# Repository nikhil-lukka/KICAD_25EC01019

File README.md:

[Exercise 0: Pre-KiCad SPICE Verification (LTspice)]

* Circuit Modeling (L1): Simulated a discrete CMOS inverter utilizing Q1

  (2N7000 NMOS) and Q2 (BS250 PMOS) driving an output LED and current-limiting

  resistor (R1) at VDD = 5 V.

* DC Transfer Analysis (L2): Swept VIN from 0 V to 5 V (0.01 V steps) to

  extract the switching threshold Vm (VOUT = VDD/2) and evaluated dead-zone

  behavior at VDD = 5 V vs. VDD = 9 V.

* Transient & Load Metrics (L3): Measured static LED current (I_LED) at

  VIN = 0 V against theoretical (VDD - V_F)/R1, and extracted 10-90% rise (t_r)

  and fall (t_f) times using a 1 kHz pulse input.

* Python Post-Processing & Scaling Comparison (L4-L5): Reproduced the Voltage

  Transfer Characteristic (VTC) at 300 DPI via pandas and compared normalized

  VTC curves (VOUT/VDD vs. VIN/VDD) against a 65 nm integrated CMOS inverter.

[Exercise 1: Schematic Capture & ERC (KiCad Schematic Editor)]

* Constructed the full circuit schematic (<roll>_INV.kicad_sch) with Q2 oriented

  so its source connects to the +5V rail.

* Configured power distribution nets (+5V, GND) with PWR_FLAG symbols and

  routed wiper (POT_W) and input (VIN) nets to header J2.

* Verified schematic integrity with 0 ERC errors and 0 warnings.

[Exercise 2: Footprint Assignment & Pinout Verification]

* Cross-referenced physical package pinouts (Source, Gate, Drain) from the

  manufacturer datasheets for the 2N7000 and BS250 against KiCad symbol pin

  numbering.

* Assigned all eight component footprints and synchronized schematic changes

  to the PCB editor (F8) with 0 errors and 0 warnings.

[Exercise 3: PCB Layout, Routing & DRC (KiCad PCB Editor)]

* Board Geometry: Defined a 50 x 40 mm board outline on Edge.Cuts with four M3

  mounting holes inset 4 mm from the corners.

* Routing & Copper Pour: Assigned +5V and GND to a dedicated Power net class,

  routed all signal/power tracks, and poured a bottom-layer (B.Cu) ground

  plane with thermal reliefs.

* Silkscreen & Verification: Added board identification (CMOS INVERTER and

  roll number) on F.Silkscreen (>= 1 mm clearance from board edges) and achieved

  0 DRC violations, 0 unconnected items, and 0 schematic parity errors.

[Exercise 4: Manufacturing Outputs (GerbView & BOM)]

* Generated Gerber plot files and drill files into gerbers/.

* Visually inspected alignment, drill hits, and silkscreen layers in GerbView.

* Exported the Bill of Materials (CSV) and packaged the fabrication archive

  (<roll>_INV_gerbers.zip).

[Exercise 5: Design Explorations (Optional)]

* Explored single-variable hardware modifications through simulation, layout,

  and Gerber generation:

  1. Cascading a second inverter stage to form a non-inverting buffer.

  2. Reconfiguring the LED load to active-low operation.

  3. Increasing minimum trace/copper clearance to 0.4 mm for low-cost

     fabrication rules.

  4. Replacing the onboard trimpot with a 2-pin external input header and

     minimizing board area.

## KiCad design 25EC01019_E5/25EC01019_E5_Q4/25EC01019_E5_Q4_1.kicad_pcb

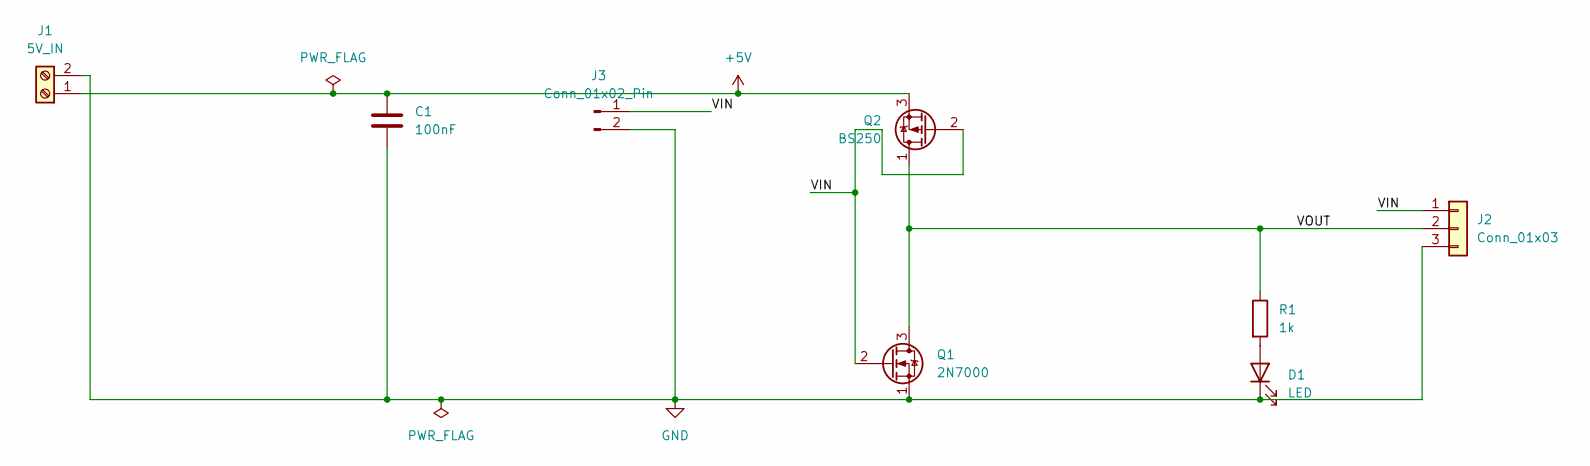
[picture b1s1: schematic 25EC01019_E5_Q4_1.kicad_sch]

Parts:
C1: 100nF; C_Disc_D5.0mm_W2.5mm_P5.00mm
D1: LED; LED_D3.0mm
J1: 5V_IN; TerminalBlock_Phoenix_MKDS-1,5-2-5.08_1x02_P5.08mm_Horizont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
J2: Conn_01x03; PinHeader_1x03_P2.54mm_Vertical
J3: Conn_01x02_Pin; PinHeader_1x02_P2.54mm_Vertical
Q1: 2N7000; TO-92_Inline
Q2: BS250; TO-92_Inline
R1: 1k; R_Axial_DIN0207_L6.3mm_D2.5mm_P10.16mm_Horizontal

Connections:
+5V: C1.1, J1.1, Q2.3 (S)
/VIN: J2.1, J3.1, Q1.2 (G), Q2.2 (G)
/VOUT: J2.2, Q1.3 (D), Q2.1 (D), R1.1
GND: C1.2, D1.1 (K), J1.2, J2.3, J3.2, Q1.1 (S)
unnamed: D1.2 (A), R1.2

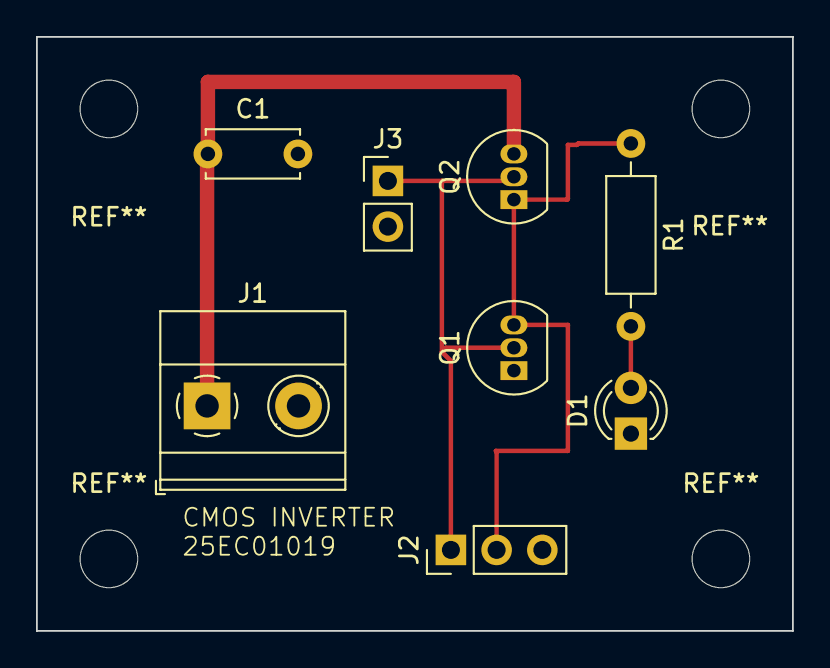
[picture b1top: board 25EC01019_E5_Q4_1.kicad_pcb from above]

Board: 2 copper layers, 42.0 x 33.0 mm, 8 parts (0 on the bottom side), 5 nets.

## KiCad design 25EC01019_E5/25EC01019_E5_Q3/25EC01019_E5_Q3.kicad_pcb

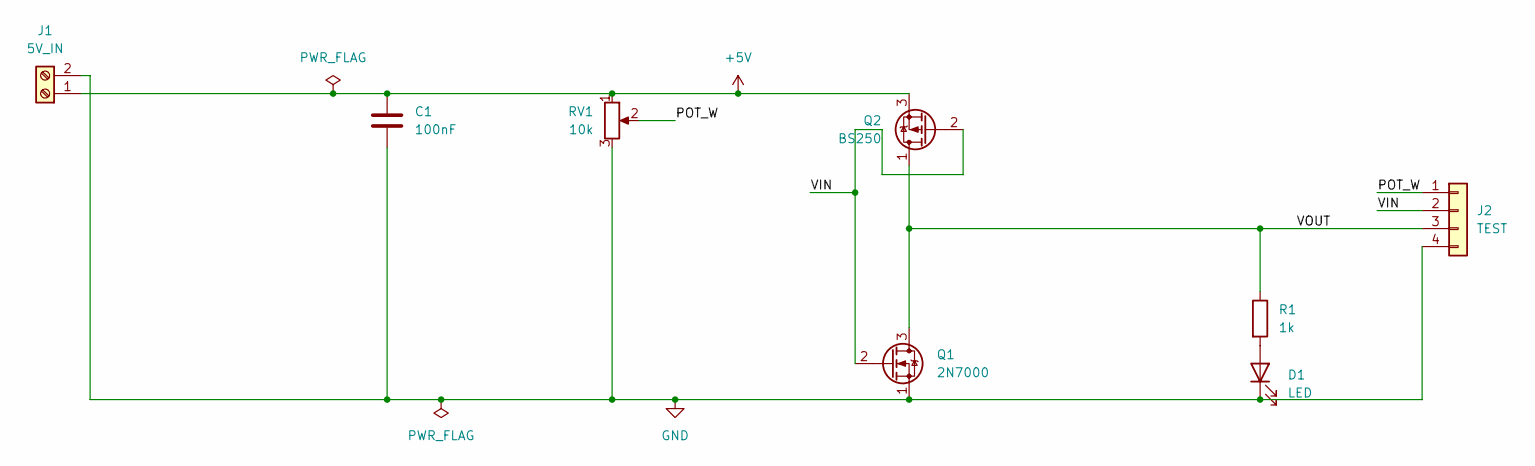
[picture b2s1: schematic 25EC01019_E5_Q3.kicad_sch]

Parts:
C1: 100nF; C_Disc_D5.0mm_W2.5mm_P5.00mm
D1: LED; LED_D3.0mm
J1: 5V_IN; TerminalBlock_Phoenix_MKDS-1,5-2-5.08_1x02_P5.08mm_Horizont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
J2: TEST; PinHeader_1x04_P2.54mm_Vertical
Q1: 2N7000; TO-92_Inline_Wide
Q2: BS250; TO-92_Inline_Wide
R1: 1k; R_Axial_DIN0207_L6.3mm_D2.5mm_P10.16mm_Horizontal
RV1: 10k; Potentiometer_Bourns_3386P_Vertical

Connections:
+5V: C1.1, J1.1, Q2.3 (S), RV1.1
/POT_W: J2.1, RV1.2
/VIN: J2.2, Q1.2 (G), Q2.2 (G)
/VOUT: J2.3, Q1.3 (D), Q2.1 (D), R1.1
GND: C1.2, D1.1 (K), J1.2, J2.4, Q1.1 (S), RV1.3
unnamed: D1.2 (A), R1.2

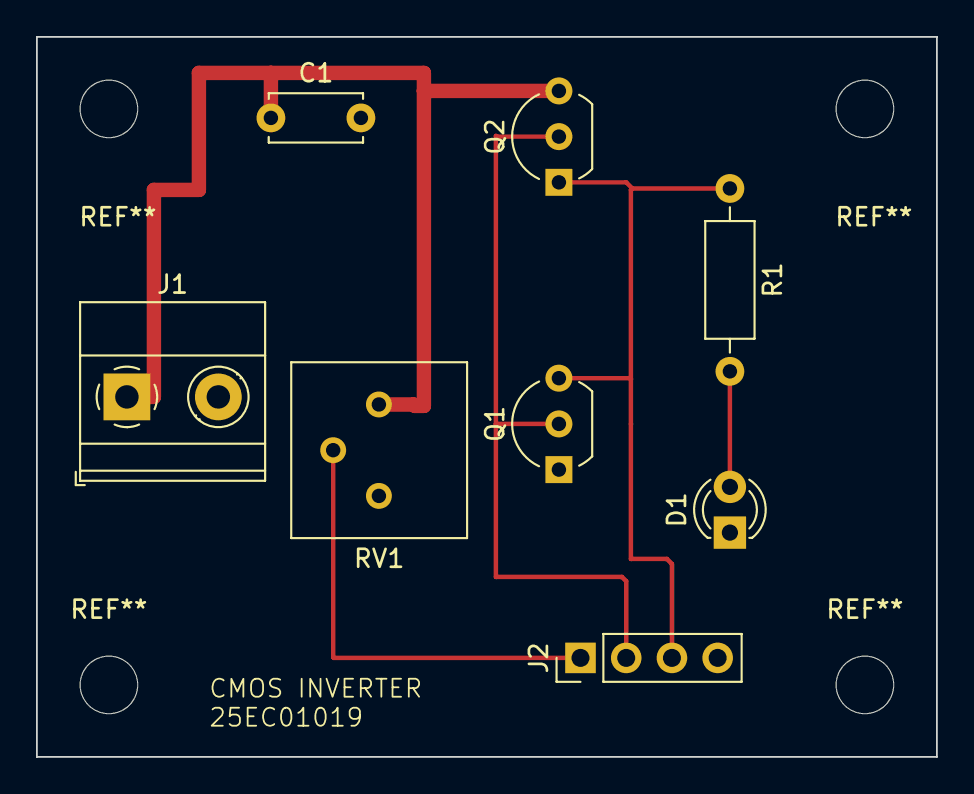
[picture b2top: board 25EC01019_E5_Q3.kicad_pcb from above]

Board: 2 copper layers, 50.0 x 40.0 mm, 8 parts (0 on the bottom side), 6 nets.
